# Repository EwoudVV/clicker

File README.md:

# Clicker

A two-button wireless remote for presentations. I wanted something small that I could use to change slides without staying next to my computer. The buttons default to left and right arrow, but they can be changed to other keys or shortcuts over USB.

## How it works

There are two boards. The battery-powered remote has two Kailh Choc V1 switches and an ESP32-C3. It sends the button states to an ESP32-S3 receiver over ESP-NOW. The receiver plugs into the computer through USB-C and acts as a USB keyboard, so it does not need a separate keyboard driver. The wireless link does not need a router.

Both boards have BOOT and RESET buttons, a programming header, and status LEDs. The remote also has a power switch, a battery connector, and a USB-C charging port. Both PCBs are two-layer boards.

### Remote PCB

### Receiver PCB

## Using it

After flashing and pairing the boards:

1. Plug the receiver into the computer with a USB data cable.
2. Turn on the remote and open the presentation. Click the presentation window so it has keyboard focus.
3. Button 1 sends left arrow for the previous slide. Button 2 sends right arrow for the next slide. Use the remapping commands below if the presentation software expects different keys.
4. Turn off the remote when finished. The current firmware keeps the radio awake while it is on.

Holding a button holds the corresponding keyboard key. If the wireless link stops, the receiver releases the keys after 300 ms to avoid a stuck key.

### First setup

The [firmware guide](firmware/README.md) has the build commands, board settings, upload instructions, and pin assignments. The remote and receiver use different ESP32 targets, so each needs its own sketch.

Once both are flashed, open each board's USB serial console at 115200 baud with newline enabled. Send `status` to get its MAC address. Generate a shared pairing key on the computer:

```sh
python3 -c 'import secrets; print(secrets.token_hex(16))'
```

Send `pair <receiver-MAC> <key>` to the remote, then `pair <remote-MAC> <same-key>` to the receiver. Replace the placeholders with the actual addresses and the generated 32-character key. Pairing is saved through restarts. `unpair` clears it.

### Changing the buttons

Send these commands to the receiver's USB serial console to use page up and page down:

```text
map 1 pageup
map 2 pagedown
status
```

For the original slide controls, use `map 1 left` and `map 2 right`. Changes save immediately and do not need a firmware upload. Letters, other keyboard keys, and modifier combinations are supported too. The [firmware guide](firmware/README.md#remapping) lists the options. Media keys and sequences of multiple key presses are not implemented.

## Parts and assembly

The [full BOM](BOM.csv) covers one remote and one receiver, including the battery, case screws, and PCB orders. It includes supplier links, quantities used, and quantities bought. Some parts come in minimum packs, and each PCB quote is for five boards.

The submitted parts estimate is **$40.78**, plus a **$23.54 provisional shipping and tax allowance**, for **$64.32**. These are the submission quotes, not current checkout prices. Final shipping, taxes, and PCB discounts still need checking before ordering.

### Bill of materials

Quantities used are for one working pair. Order quantities include the supplier packs and spare boards. Prices are in USD.

| Part | Used | Order | Unit price | Total | Supplier |
| --- | ---: | --- | ---: | ---: | --- |
| ESP32-S3-WROOM-1-N4 | 1 | 1 each | $4.15 | $4.15 | [LCSC](https://www.lcsc.com/product-detail/C2913197.html) |
| ESP32-C3-WROOM-02-N4 | 1 | 1 each | $3.32 | $3.32 | [LCSC](https://www.lcsc.com/product-detail/C2934560.html) |
| AP2112K-3.3TRG1 (5 pack) | 2 | 1 pack of 5 | $0.86 | $0.86 | [LCSC](https://www.lcsc.com/product-detail/C51118.html) |
| TYPE-C-31-M-12 (5 pack) | 2 | 1 pack of 5 | $0.86 | $0.86 | [LCSC](https://www.lcsc.com/product-detail/C165948.html) |
| Microchip MCP73831T-2ATI/OT | 1 | 2 each | $1.40 | $2.80 | [LCSC](https://www.lcsc.com/product-detail/C14879.html) |
| Omron B3U-1000P (5 pack) | 4 | 2 pack of 5 | $0.94 | $1.88 | [LCSC](https://www.lcsc.com/product-detail/C231329.html) |
| JST B2B-PH-K-S(LF)(SN) (20 pack) | 1 | 1 pack of 20 | $0.71 | $0.71 | [LCSC](https://www.lcsc.com/product-detail/C131337.html) |
| Kailh Choc V1 red switches | 2 | 2 each | $0.60 | $1.20 | [Keebio](https://keeb.io/products/kailh-choc-low-profile-switches-v1?variant=40343498227806) |
| 0603WAF1001T5E (100 pack) | 3 | 1 pack of 100 | $0.26 | $0.26 | [LCSC](https://www.lcsc.com/product-detail/C21190.html) |
| Yageo RC0603FR-0710KL (100 pack) | 2 | 1 pack of 100 | $0.34 | $0.34 | [LCSC](https://www.lcsc.com/product-detail/C98220.html) |
| 0603WAF1003T5E (100 pack) | 2 | 1 pack of 100 | $0.31 | $0.31 | [LCSC](https://www.lcsc.com/product-detail/C25803.html) |
| 0603WAF2001T5E (100 pack) | 1 | 1 pack of 100 | $0.24 | $0.24 | [LCSC](https://www.lcsc.com/product-detail/C22975.html) |
| Yageo CC0603KRX7R9BB104 (50 pack) | 2 | 1 pack of 50 | $0.62 | $0.62 | [LCSC](https://www.lcsc.com/product-detail/C14663.html) |
| CL10A106MQ8NNNC (10 pack) | 2 | 1 pack of 10 | $0.23 | $0.23 | [LCSC](https://www.lcsc.com/product-detail/C1691.html) |
| CL10B105KO8NNNC (50 pack) | 2 | 1 pack of 50 | $1.06 | $1.06 | [LCSC](https://www.lcsc.com/product-detail/C59782.html) |
| M2 x 6 mm stainless steel screws (25 pack) | 8 | 1 pack of 25 | $3.49 | $3.49 | [Keebio](https://keeb.io/products/m2-screws-and-standoffs?variant=47874887558) |
| SS14 Schottky diodes (50 pack) | 2 | 1 pack of 50 | $0.94 | $0.94 | [LCSC](https://www.lcsc.com/product-detail/C2480.html) |
| Kingbright APT1608SURCK red LEDs (5 pack) | 3 | 1 pack of 5 | $0.63 | $0.63 | [LCSC](https://www.lcsc.com/product-detail/C5875723.html) |
| C&K OS102011MS2QN1 power switch | 1 | 1 each | $0.66 | $0.66 | [LCSC](https://www.lcsc.com/product-detail/C221829.html) |
| 1x3 2.54 mm pin headers (5 pack) | 2 | 1 pack of 5 | $0.12 | $0.12 | [LCSC](https://www.lcsc.com/product-detail/C32713269.html) |
| Adafruit 1578 protected 3.7 V 500 mAh battery | 1 | 1 each | $7.95 | $7.95 | [Mouser](https://www.mouser.com/en/ProductDetail/Adafruit/1578?qs=GURawfaeGuBBv%2Fo5AsyERQ%3D%3D) |
| Receiver PCB (5 board batch) | 1 | 1 batch of 5 boards | $4.00 | $4.00 | [JLCPCB](https://cart.jlcpcb.com/quote) |
| Remote PCB (5 board batch) | 1 | 1 batch of 5 boards | $4.00 | $4.00 | [JLCPCB](https://cart.jlcpcb.com/quote) |
| 0603WAF5101T5E (100 pack) | 4 | 1 pack of 100 | $0.15 | $0.15 | [LCSC](https://www.lcsc.com/product-detail/C23186.html) |
| Printed case parts | 4 | 4 printed part | $0.00 | $0.00 | [Already owned filament](enclosures/stl) |
| Printed keycaps | 2 | 2 printed part | $0.00 | $0.00 | [Already owned filament](enclosures/stl) |
| Tax and shipping allowance |  | 1 allowance | $23.54 | $23.54 | [Multiple suppliers](https://halflife.hackclub.com/projects/cmuo5o3bs001h01q34f93breu) |
| **Total estimate** | | | | **$64.32** | |

### Assembly

The board-level component lists are [remote BOM](remote/production/bom.csv) and [receiver BOM](receiver/production/bom.csv). The full BOM records the supplier substitutions selected during sourcing, including the LEDs and power switch that still need checking before purchase.

Solder the small surface-mount parts first, then the modules and connectors. Check orientation and inspect for bridges before powering either board. Bring up the boards on current-limited USB power and check the 3.3 V rails before flashing them.

The remote currently has a 2k charge-program resistor, which sets roughly 500 mA. Check this against the selected battery's charging limit and change the resistor if needed before connecting the battery. Also check the battery connector polarity. Charging, battery runtime, and operation as the battery discharges still need testing.

## Cases

Both boards sit on printed supports and are held down by the lids. Each case uses four M2 x 6 mm screws. The remote's battery sits beside the PCB to keep the case thinner.

The switch centres are 16.5 mm apart, so I made narrower printed keycaps with a 1.1 mm gap. Print the stem-fit sample before the keycaps and check that they seat without forcing the switch sockets.

- [Print plate](enclosures/clicker-print-plate.3mf)
- [Individual STL files](enclosures/stl)
- [Case download with STEP models and assembly instructions](enclosures/clicker-enclosures.zip)

Use PLA or PETG, around 0.16 to 0.20 mm layers, and at least three walls. Select the printer and material in the slicer. Check the USB openings, screw holes, and keycap stems in the slice preview before printing.

## Design files and progress

The editable KiCad projects are in [remote](remote) and [receiver](receiver). Ready-to-upload Gerber ZIPs are in [remote/production](remote/production/gerbers.zip) and [receiver/production](receiver/production/gerbers.zip). The [journal](journal.md) has the design progress.

The boards are routed, the firmware has compiled, and the cases have been checked in CAD. Nothing has been assembled or physically tested yet. The next step is to check the remaining part choices, build a pair, and test charging, button response, wireless range, and case fit.

Designed by EVV

*Made for Hack Club Half Life*

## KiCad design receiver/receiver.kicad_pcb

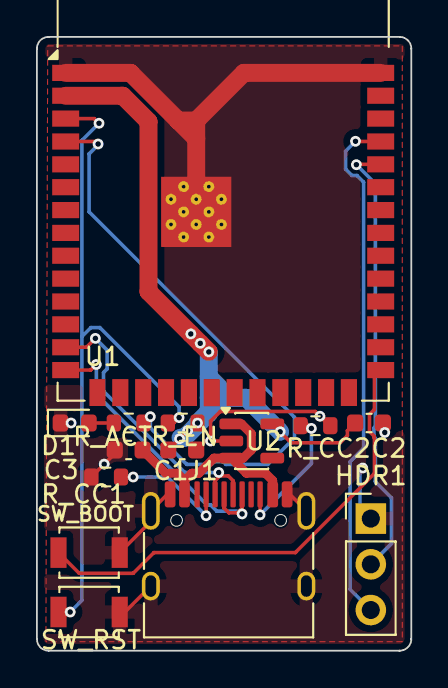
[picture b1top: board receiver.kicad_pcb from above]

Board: 2 copper layers, 20.8 x 34.1 mm, 14 parts (0 on the bottom side), 13 nets.

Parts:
C1: 100nF; C_0603_1608Metric
C2: 10uF; C_0603_1608Metric
C3: 1uF; C_0603_1608Metric
D1: ACT; LED_0603_1608Metric
HDR1: DEBUG; PinHeader_1x03_P2.54mm_Vertical
J1: USB-C; USB_C_Receptacle_HRO_TYPE-C-31-M-12
R_ACT: 1k; R_0603_1608Metric
R_CC1, R_CC2: 5.1k; R_0603_1608Metric
R_EN: 10k; R_0603_1608Metric
SW_BOOT: BOOT; SW_SPST_B3U-1000P
SW_RST: RESET; SW_SPST_B3U-1000P
U1: ESP32-S3-WROOM-1
U2: AP2112K-3.3; SOT-23-5

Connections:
3v3: C1.1, C2.1, R_EN.2, U1.2, U2.5
ACT_A: D1.2, R_ACT.2
BOOT_NET: SW_BOOT.1, U1.27
CC1: J1.A5, R_CC1.1
CC2: J1.B5, R_CC2.1
EN_NET: R_EN.1, SW_RST.1, U1.3
GND: C1.2, C2.2, C3.2, D1.1, HDR1.1, J1.A1, J1.A12, J1.B1, J1.B12, J1.SH, R_CC1.2, R_CC2.2, SW_BOOT.2, SW_RST.2, U1.1, U1.40, U1.41, U2.2
LED_ACT: R_ACT.1, U1.4
UART_RX: HDR1.2, U1.36
UART_TX: HDR1.3, U1.37
USB_DN: J1.A7, J1.B7, U1.13
USB_DP: J1.A6, J1.B6, U1.14
VBUS: C3.1, J1.A4, J1.A9, J1.B4, J1.B9, U2.1, U2.3

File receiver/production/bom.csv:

Item #,Designator,Qty,Manufacturer,Mfg Part #,Description,Package,Type
1,U1,1,Espressif,ESP32-S3-WROOM-1-N4,"WiFi+BLE5 module, 4MB flash, PCB antenna, native USB",SMD module,Module
2,U2,1,Diodes Inc,AP2112K-3.3TRG1,"600mA low-dropout regulator, 3.3V fixed",SOT-23-5,IC
3,J1,1,HRO,TYPE-C-31-M-12,"USB Type-C receptacle, 16P, USB2.0+PD",SMD,Connector
4,HDR1,1,Generic,1x03 2.54mm pin header,"Pin header 1x3, 2.54mm pitch, vertical",THT,Connector
5,"SW_BOOT, SW_RST",2,Omron,B3U-1000P,"Tactile switch, top actuated",SMD,Switch
6,D1,1,Everlight,19-213/R6C-AL1M2VY/3T,Red 0603 LED,0603,LED
7,R_ACT,1,UNI-ROYAL,0603WAF1001T5E,1k ohm 1% 1/10W,0603,Resistor
8,"R_CC1, R_CC2",2,UNI-ROYAL,0603WAF5101T5E,5.1k ohm 1% 1/10W,0603,Resistor
9,R_EN,1,UNI-ROYAL,0603WAF1002T5E,10k ohm 1% 1/10W,0603,Resistor
10,C1,1,Samsung,CL10B104KB8NNNC,100nF 50V X7R ceramic,0603,Capacitor
11,C2,1,Samsung,CL10A106MQ8NNNC,10uF 6.3V X5R ceramic,0603,Capacitor
12,C3,1,Samsung,CL10B105KO8NNNC,1uF 25V X7R ceramic,0603,Capacitor

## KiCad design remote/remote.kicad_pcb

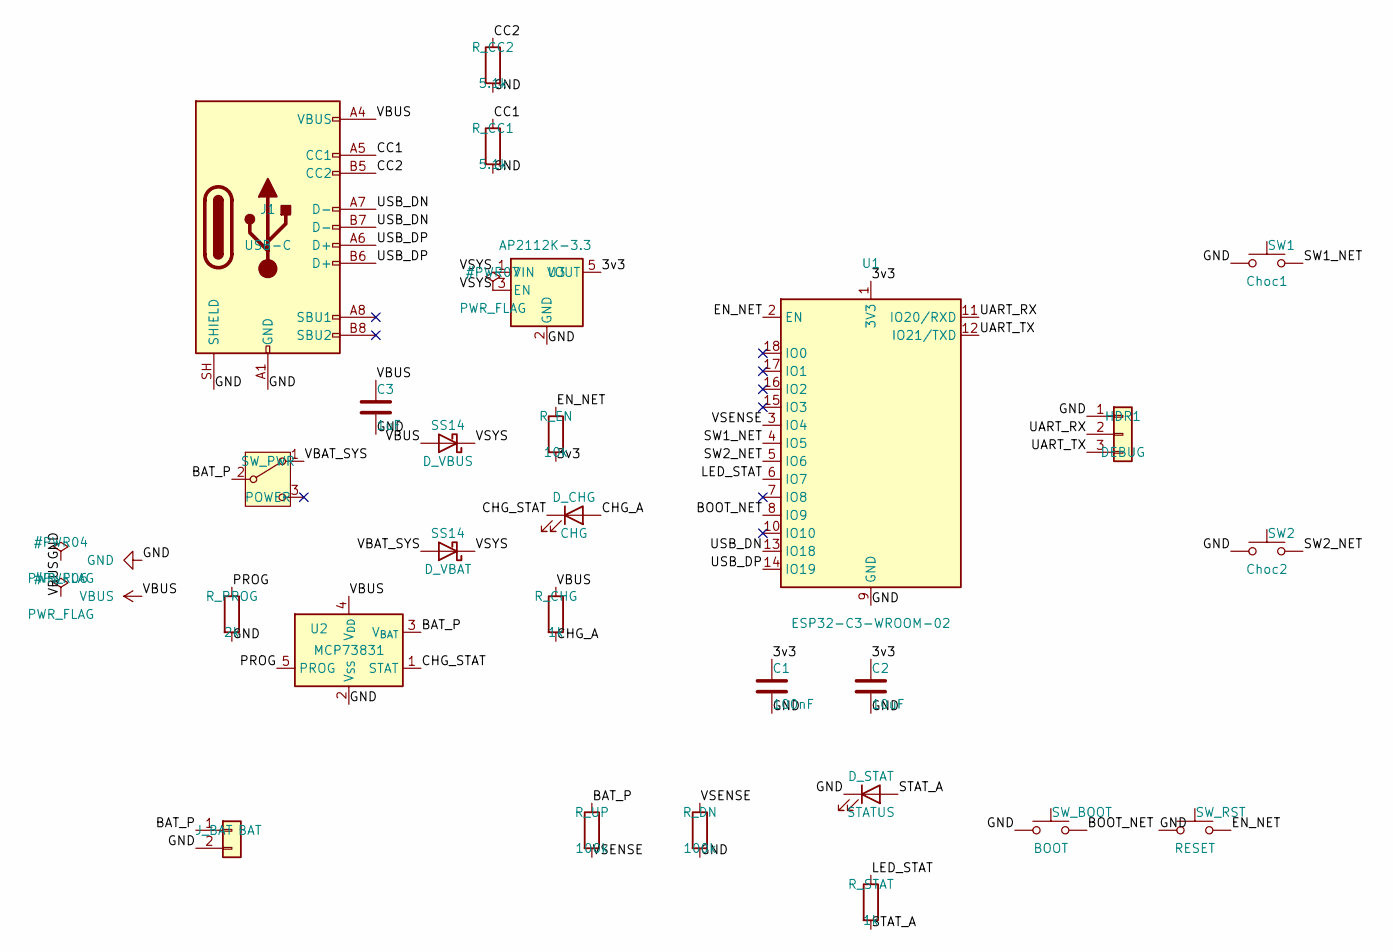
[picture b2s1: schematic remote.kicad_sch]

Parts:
C1: 100nF; C_0603_1608Metric
C2: 10uF; C_0603_1608Metric
C3: 1uF; C_0603_1608Metric
D_CHG: CHG; LED_0603_1608Metric
D_STAT: STATUS; LED_0603_1608Metric
D_VBAT: SS14; D_SMA
D_VBUS: SS14; D_SMA
HDR1: DEBUG; PinHeader_1x03_P2.54mm_Vertical
J1: USB-C; USB_C_Receptacle_HRO_TYPE-C-31-M-12
J_BAT: BAT; JST_PH_B2B-PH-K_1x02_P2.00mm_Vertical
R_CC1, R_CC2: 5.1k; R_0603_1608Metric
R_CHG: 1k; R_0603_1608Metric
R_DN: 100k; R_0603_1608Metric
R_EN: 10k; R_0603_1608Metric
R_PROG: 2k; R_0603_1608Metric
R_STAT: 1k; R_0603_1608Metric
R_UP: 100k; R_0603_1608Metric
SW1: Choc1; Choc_V1_PG1350
SW2: Choc2; Choc_V1_PG1350
SW_BOOT: BOOT; SW_SPST_B3U-1000P
SW_PWR: POWER; SW_Slide_SPDT_Straight_CK_OS102011MS2Q
SW_RST: RESET; SW_SPST_B3U-1000P
U1: ESP32-C3-WROOM-02
U2: MCP73831; SOT-23-5
U3: AP2112K-3.3; SOT-23-5

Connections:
3v3: C1.1, C2.1, R_EN.2, U1.1 (3V3), U3.5 (VOUT)
BAT_P: J_BAT.1, R_UP.1, SW_PWR.2 (B), U2.3 (V_{BAT})
BOOT_NET: SW_BOOT.2, U1.8 (IO9)
CC1: J1.A5 (CC1), R_CC1.1
CC2: J1.B5 (CC2), R_CC2.1
CHG_A: D_CHG.2 (A), R_CHG.2
CHG_STAT: D_CHG.1 (K), U2.1 (STAT)
EN_NET: R_EN.1, SW_RST.2, U1.2 (EN)
LED_STAT: R_STAT.1, U1.6 (IO7)
PROG: R_PROG.1, U2.5 (PROG)
STAT_A: D_STAT.2 (A), R_STAT.2
SW1_NET: SW1.2, U1.4 (IO5)
SW2_NET: SW2.2, U1.5 (IO6)
UART_RX: HDR1.2, U1.11 (IO20/RXD)
UART_TX: HDR1.3, U1.12 (IO21/TXD)
USB_DN: J1.A7 (D-), J1.B7 (D-), U1.13 (IO18)
USB_DP: J1.A6 (D+), J1.B6 (D+), U1.14 (IO19)
VBAT_SYS: D_VBAT.2 (A), SW_PWR.1 (A)
VSENSE: R_DN.1, R_UP.2, U1.3 (IO4)

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
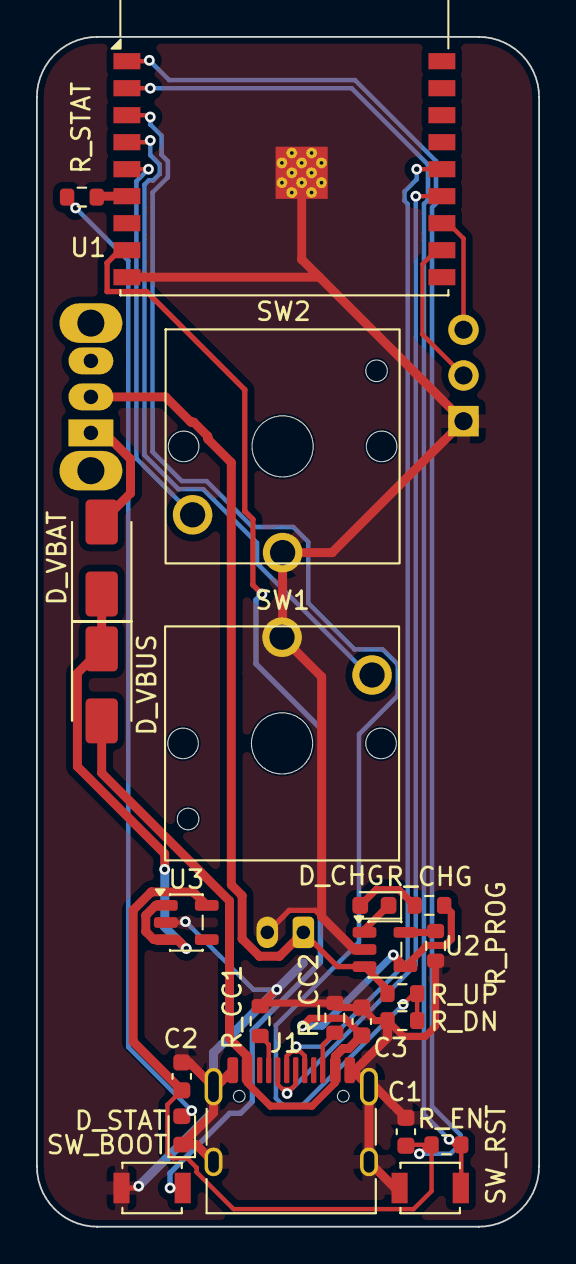
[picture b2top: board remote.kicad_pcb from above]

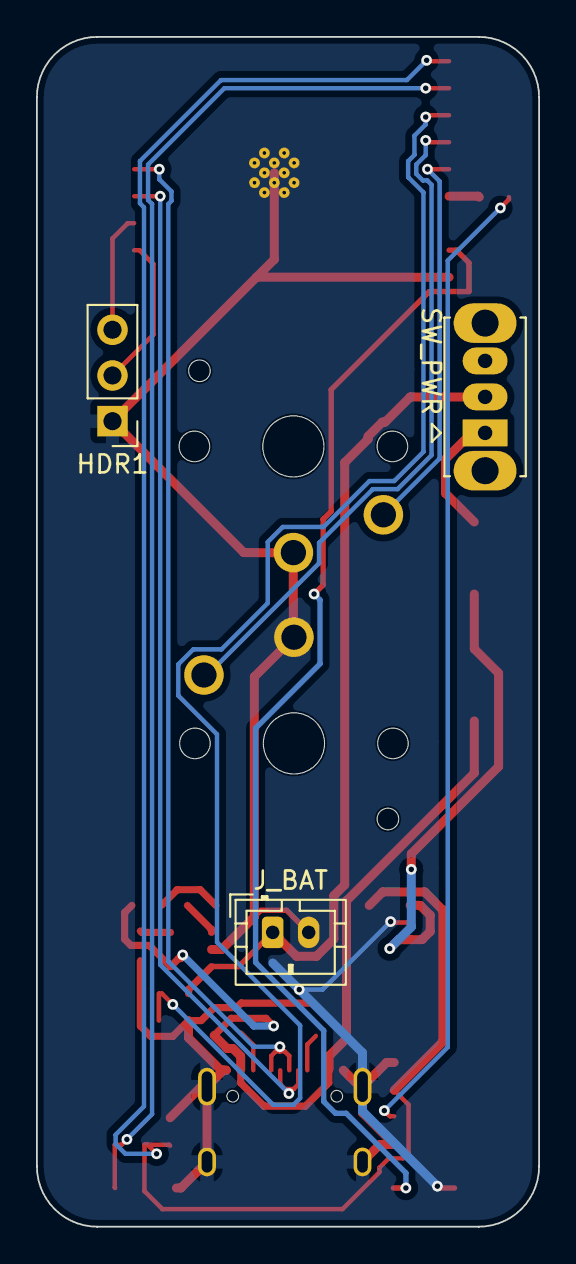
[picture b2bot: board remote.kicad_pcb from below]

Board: 2 copper layers, 27.9 x 66.1 mm, 26 parts (3 on the bottom side), 22 nets.
